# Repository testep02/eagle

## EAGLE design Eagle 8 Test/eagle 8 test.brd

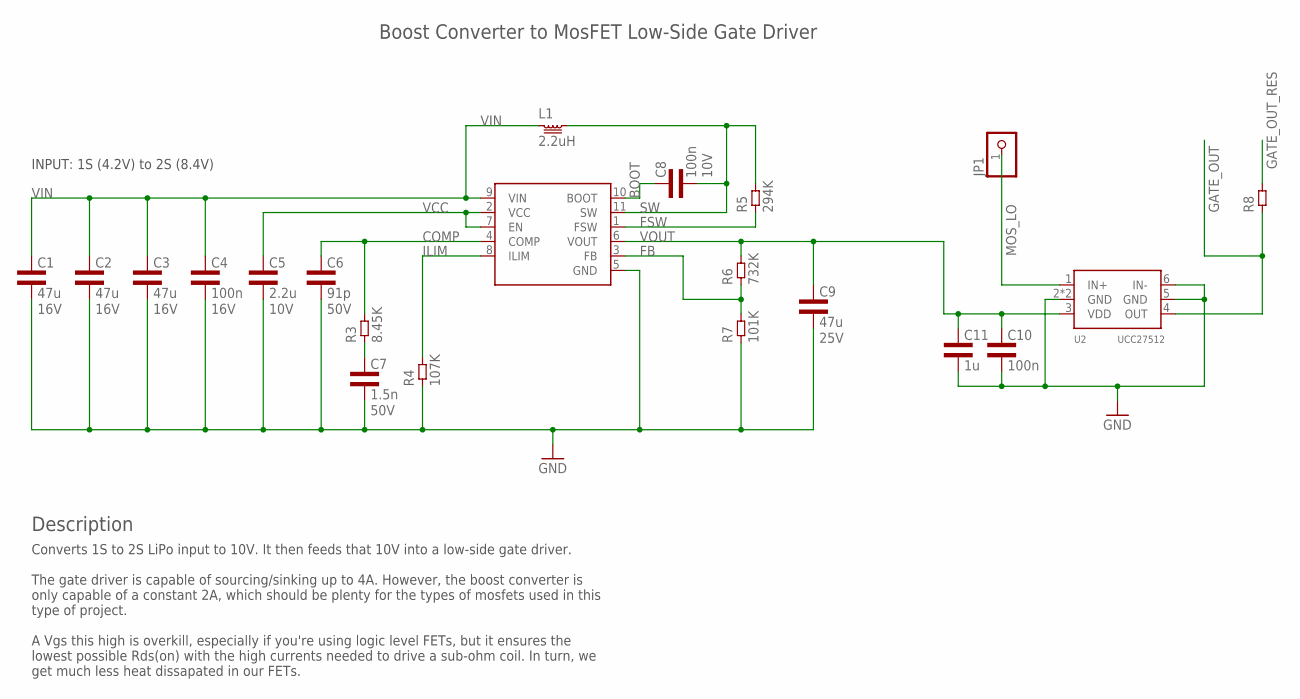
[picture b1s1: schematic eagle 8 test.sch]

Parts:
C1, C2, C3: 47u; 1210L3; VOLTAGE 16V
C4: 100n; 0402L3; VOLTAGE 16V
C5: 2.2u; 0603L3; VOLTAGE 10V
C6: 91p; 0805L3; VOLTAGE 50V
C7: 1.5n; 0805L3; VOLTAGE 50V
C8: 100n; 0402L3; VOLTAGE 10V
C9: 47u; 1206L3; VOLTAGE 25V
C10: 100n; 0603L3
C11: 1u; 0805L3
JP1: PINHD-1X1; 1X01
L1: 2.2uH; 9.2X8.5
R3: 8.45K; 0402L3
R4: 107K; 1206L3
R5: 294K; 1206L3
R6: 732K; 0402L3
R7: 101K; 0805L3
R8: RES1206L3; 1206L3
U1: TPS61089; VQFN-11
U2: UCC27512; S-PWSON-N6

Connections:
BOOT: C8.P$1 (1), U1.10 (BOOT)
COMP: C6.1, R3.P$2 (2), U1.4 (COMP)
COMP_RES: C7.1, R3.P$1 (1)
FB: R6.P$1 (1), R7.2, U1.3 (FB)
FSW: R5.1, U1.1 (FSW)
GATE_OUT: R8.1, U2.4 (OUT)
GATE_OUT_RES: R8.2
GND: C1.P$2 (2), C2.P$2 (2), C3.P$2 (2), C4.P$2 (2), C5.P$2 (2), C6.2, C7.2, C9.2, C10.P$2 (2), C11.2, R4.1, R7.1, U1.5 (GND), U2.2 (GND), U2.5 (GND), U2.6 (IN-), U2.TP (GND)
ILIM: R4.2, U1.8 (ILIM)
MOS_LO: JP1.1, U2.1 (IN+)
SW: C8.P$2 (2), L1.2, R5.2, U1.11 (SW)
VCC: C5.P$1 (1), U1.2 (VCC), U1.7 (EN)
VIN: C1.P$1 (1), C2.P$1 (1), C3.P$1 (1), C4.P$1 (1), L1.1, U1.9 (VIN)
VOUT: C9.1, C10.P$1 (1), C11.1, R6.P$2 (2), U1.6 (VOUT), U2.3 (VDD)

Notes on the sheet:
INPUT: 1S (4.2V) to 2S (8.4V)
Boost Converter to MosFET Low-Side Gate Driver
Description
Converts 1S to 2S LiPo input to 10V. It then feeds that 10V into a low-side gate driver. The gate driver is capable of sourcing/sinking up to 4A. However, the boost converter is only capable of a constant 2A, which should be plenty for the types of mosfets used in this type of project. A Vgs this h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

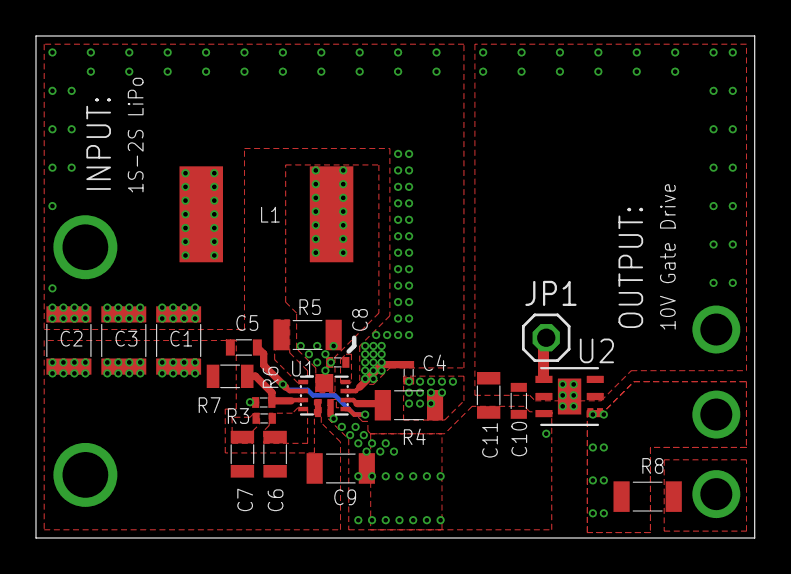
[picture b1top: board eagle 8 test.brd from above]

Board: 4 copper layers, 39.9 x 27.9 mm, 21 parts (0 on the bottom side), 13 nets.

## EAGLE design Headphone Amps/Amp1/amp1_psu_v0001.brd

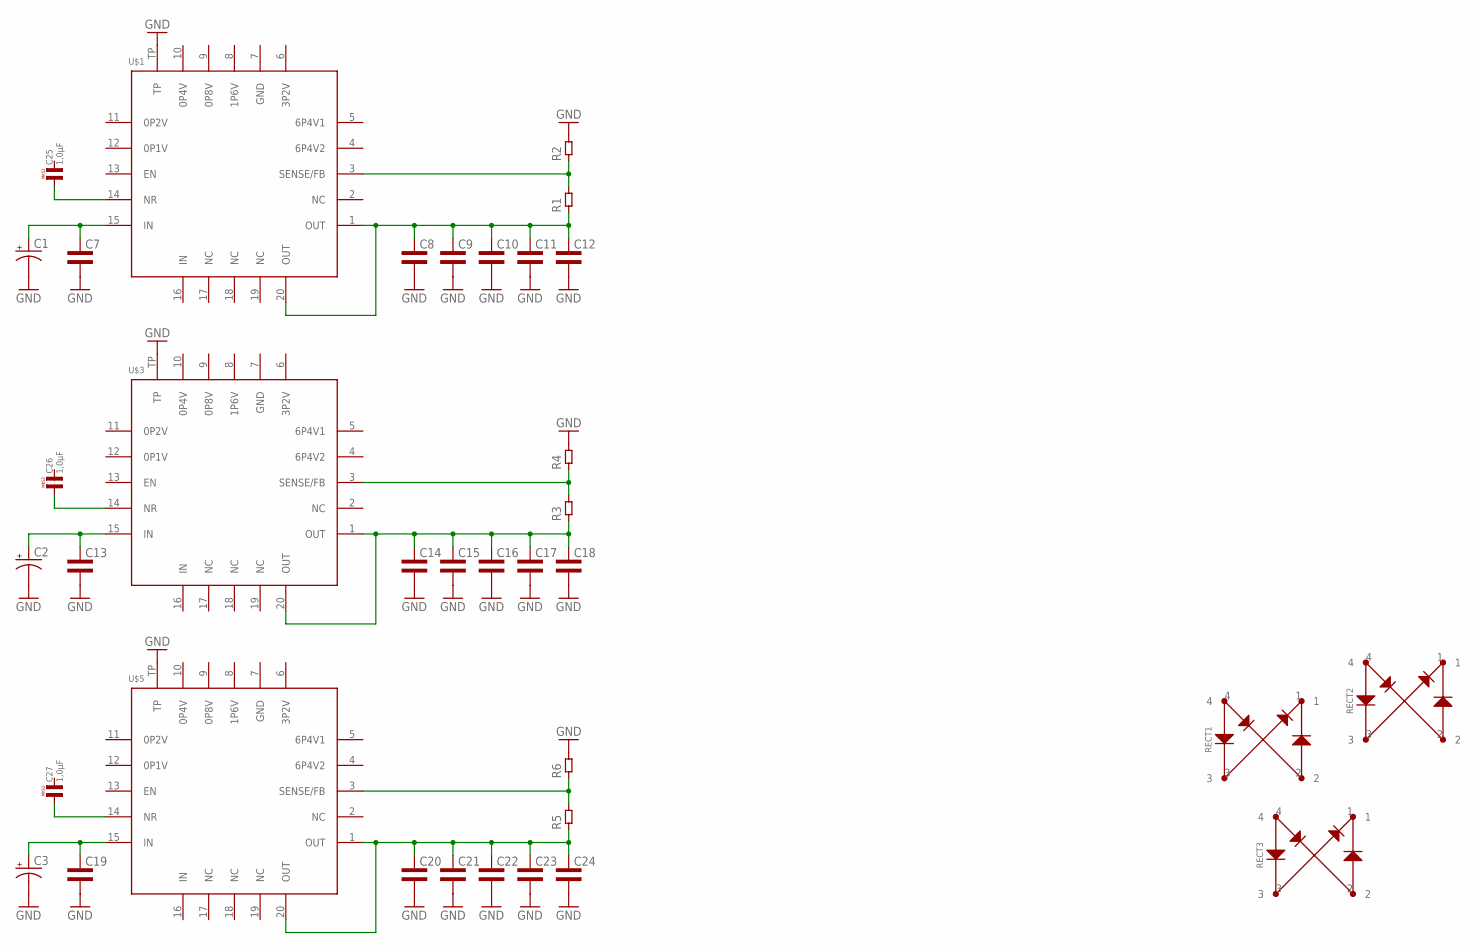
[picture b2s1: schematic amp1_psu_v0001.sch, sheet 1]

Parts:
C1, C2, C3: CPOL-USE7.5-18; E7,5-18
C7, C8, C9, C10, C11, C12, C13, C14, C15, C16, C17, C18, C19, C20, C21, C22, C23, C24: CAP0805L3; 0805L3
C25, C26, C27: 1,0µF; R5B5
R1, R2, R3, R4, R5, R6: RES0805L3; 0805L3
RECT1, RECT2, RECT3: RECTIFIER_Z4GP206; RECTIFIER_ABS-4
U$1, U$3, U$5: POWER-SUPPLY_POS_V1_TI_LDO_TPS7A4700; POWER-SUPPLY_POS_V1_TI_LDO_VQFN-20

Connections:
GND: C1.-, C2.-, C3.-, C7.2, C8.2, C9.2, C10.2, C11.2, C12.2, C13.2, C14.2, C15.2, C16.2, C17.2, C18.2, C19.2, C20.2, C21.2, C22.2, C23.2, C24.2, R2.2, R4.2, R6.2, U$1.TP, U$3.TP, U$5.TP; also elsewhere on the board
unnamed: C1.+, C7.1, U$1.15 (IN)
unnamed: C8.1, C9.1, C10.1, C11.1, C12.1, R1.1, U$1.1 (OUT), U$1.20 (OUT)
unnamed: C2.+, C13.1, U$3.15 (IN)
unnamed: C14.1, C15.1, C16.1, C17.1, C18.1, R3.1, U$3.1 (OUT), U$3.20 (OUT)
unnamed: C3.+, C19.1, U$5.15 (IN)
unnamed: C20.1, C21.1, C22.1, C23.1, C24.1, R5.1, U$5.1 (OUT), U$5.20 (OUT)
unnamed: R3.2, R4.1, U$3.3 (SENSE/FB)
unnamed: R5.2, R6.1, U$5.3 (SENSE/FB)
unnamed: R1.2, R2.1, U$1.3 (SENSE/FB)
unnamed: C25.1, U$1.14 (NR)
unnamed: C26.1, U$3.14 (NR)
unnamed: C27.1, U$5.14 (NR)

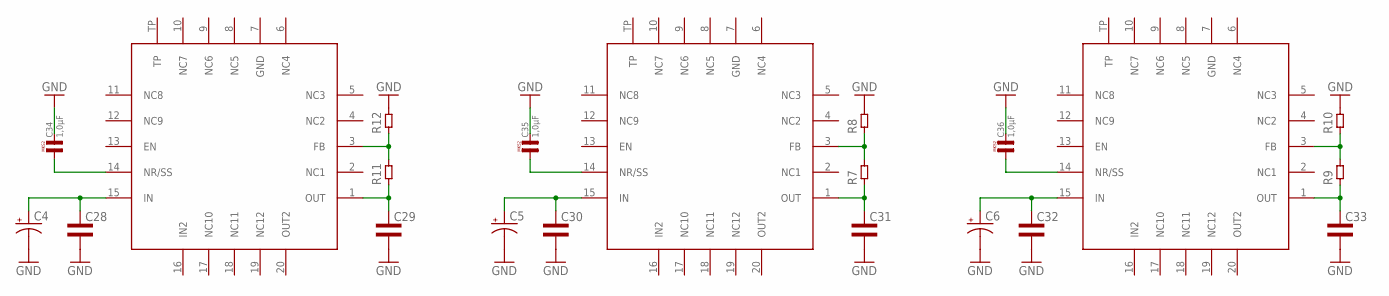
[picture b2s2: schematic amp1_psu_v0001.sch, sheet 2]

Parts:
C4, C5, C6: CPOL-USE7.5-18; E7,5-18
C28, C29, C30, C31, C32, C33: CAP0805L3; 0805L3
C34, C35, C36: 1,0µF; R5B5
R7, R8, R9, R10, R11, R12: RES0805L3; 0805L3
U$6, U$7, U$8: POWER-SUPPLY_POS_V1_TI_LDO_TPS7A3301RGWT; POWER-SUPPLY_POS_V1_TI_LDO_VQFN-20

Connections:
GND: C4.-, C5.-, C6.-, C28.2, C29.2, C30.2, C31.2, C32.2, C33.2, C34.2, C35.2, C36.2, R8.2, R10.2, R12.2; also elsewhere on the board
unnamed: C4.+, C28.1, U$6.15 (IN)
unnamed: C29.1, R11.1, U$6.1 (OUT)
unnamed: C5.+, C30.1, U$7.15 (IN)
unnamed: C31.1, R7.1, U$7.1 (OUT)
unnamed: C6.+, C32.1, U$8.15 (IN)
unnamed: C33.1, R9.1, U$8.1 (OUT)
unnamed: R11.2, R12.1, U$6.3 (FB)
unnamed: R7.2, R8.1, U$7.3 (FB)
unnamed: R9.2, R10.1, U$8.3 (FB)
unnamed: C34.1, U$6.14 (NR/SS)
unnamed: C35.1, U$7.14 (NR/SS)
unnamed: C36.1, U$8.14 (NR/SS)

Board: 2 copper layers, 57 parts (8 on the bottom side), 25 nets, no tracks yet.

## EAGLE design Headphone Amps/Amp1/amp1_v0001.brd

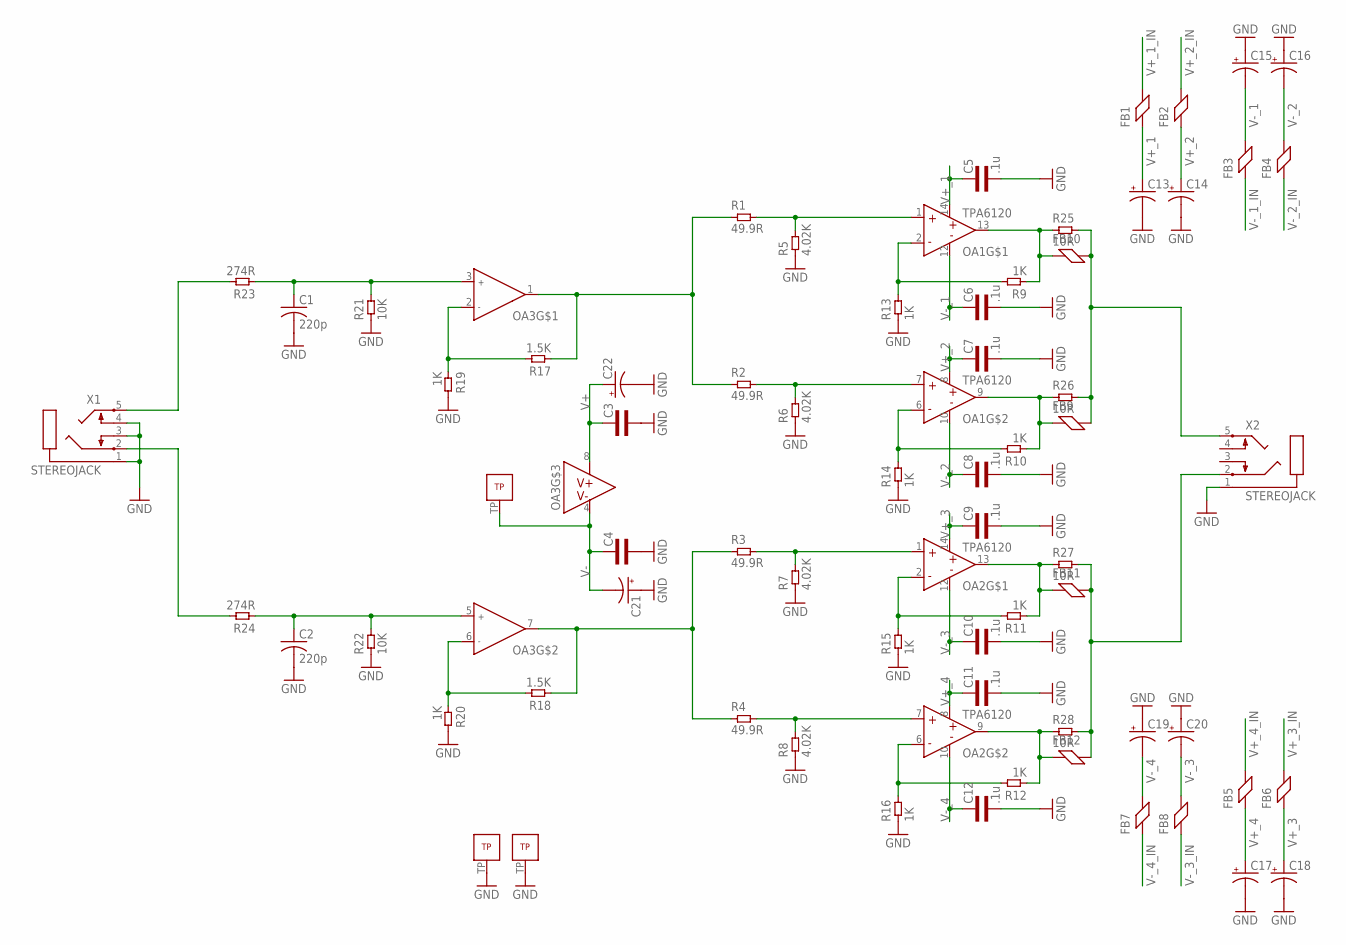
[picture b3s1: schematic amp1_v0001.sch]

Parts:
C1, C2: 220p; C025-025X050
C3, C4: CAP0603L3; 0603L3
C5, C6, C7, C8, C9, C10, C11, C12: .1u; 0603L3
C13, C14, C15, C16, C17, C18, C19, C20, C21, C22: CPOL-USE2-5; E2-5
FB1, FB2, FB3, FB4, FB5, FB6, FB7, FB8, FB9, FB10, FB11, FB12: FERRITE0805L3; 0805L3
OA1, OA2: TPA6120QFN; S-PVQFN-N14
OA3: OPA1612; S-PWSON-N8
R1, R2, R3, R4: 49.9R; 0805L3
R5, R6, R7, R8: 4.02K; 0805L3
R9, R10, R11, R12, R13, R14, R15, R16, R19, R20: 1K; 0805L3
R17, R18: 1.5K; 0805L3
R21, R22: 10K; 0805L3
R23, R24: 274R; 0805L3
R25, R26, R27, R28: 10R; 1206L3
X1, X2: STEREOJACK; STX3100

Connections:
GND: C1.2, C2.2, C3.P$2 (2), C4.P$2 (2), C5.P$2 (2), C6.P$2 (2), C7.P$2 (2), C8.P$2 (2), C9.P$2 (2), C10.P$2 (2), C11.P$2 (2), C12.P$2 (2), C13.-, C14.-, C15.+, C16.+, C17.-, C18.-, C19.+, C20.+, C21.+, C22.-, OA1.TP, OA2.TP, R5.1, R6.1, R7.1, R8.1, R13.1, R14.1, R15.1, R16.1, R19.2, R20.2, R21.1, R22.1, X1.1, X1.3, X1.4, X2.1
unnamed: OA1.1 (IN+), R1.2, R5.2
unnamed: OA1.7 (IN+), R2.2, R6.2
unnamed: OA2.1 (IN+), R3.2, R7.2
unnamed: OA2.7 (IN+), R4.2, R8.2
unnamed: FB11.1, OA2.13 (OUT), R11.1, R27.1
unnamed: FB12.1, OA2.9 (OUT), R12.1, R28.1
unnamed: FB9.1, OA1.9 (OUT), R10.1, R26.1
unnamed: FB10.1, OA1.13 (OUT), R9.1, R25.1
unnamed: OA1.2 (IN-), R9.2, R13.2
unnamed: OA1.6 (IN-), R10.2, R14.2
unnamed: OA2.2 (IN-), R11.2, R15.2
unnamed: OA2.6 (IN-), R12.2, R16.2
unnamed: FB9.2, FB10.2, R25.2, R26.2, X2.5
unnamed: OA3.1 (OUTA), R1.1, R2.1, R17.1
unnamed: FB11.2, FB12.2, R27.2, R28.2, X2.2
unnamed: OA3.7 (OUTB), R3.1, R4.1, R18.1
unnamed: OA3.6 (INB-), R18.2, R20.1
unnamed: OA3.2 (INA-), R17.2, R19.1
unnamed: C1.1, OA3.3 (INA+), R21.2, R23.1
unnamed: C2.1, OA3.5 (INB+), R22.2, R24.1
unnamed: R24.2, X1.2
unnamed: R23.2, X1.5
V+: C3.P$1 (1), C22.+, OA3.8 (V+)
V+_1: C5.P$1 (1), C13.+, FB1.1, OA1.14 (V+)
V+_1_IN: FB1.2
V+_2: C7.P$1 (1), C14.+, FB2.1, OA1.8 (V+)
V+_2_IN: FB2.2
V+_3: C9.P$1 (1), C18.+, FB6.1, OA2.14 (V+)
V+_3_IN: FB6.2
V+_4: C11.P$1 (1), C17.+, FB5.1, OA2.8 (V+)
V+_4_IN: FB5.2
V-: C4.P$1 (1), C21.-, OA3.4 (V-), OA3.TP
V-_1: C6.P$1 (1), C15.-, FB3.2, OA1.12 (V-)
V-_1_IN: FB3.1
V-_2: C8.P$1 (1), C16.-, FB4.2, OA1.10 (V-)
V-_2_IN: FB4.1
V-_3: C10.P$1 (1), C20.-, FB8.2, OA2.12 (V-)
V-_3_IN: FB8.1
V-_4: C12.P$1 (1), C19.-, FB7.2, OA2.10 (V-)
V-_4_IN: FB7.1

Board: 2 copper layers, 67 parts (9 on the bottom side), 33 nets, no tracks yet.

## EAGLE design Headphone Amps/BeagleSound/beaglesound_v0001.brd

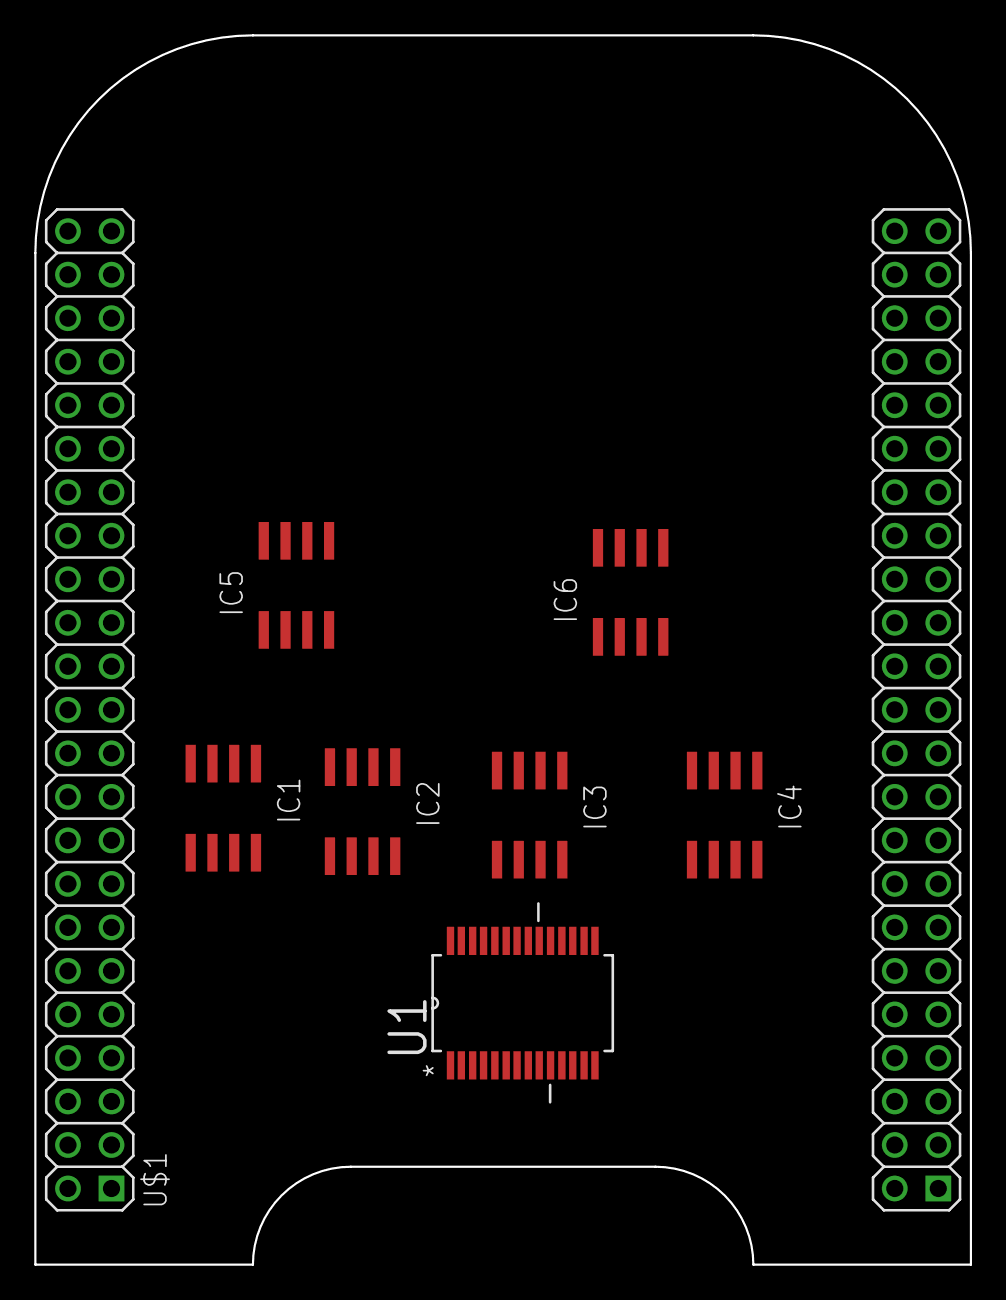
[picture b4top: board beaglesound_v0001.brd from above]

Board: 2 copper layers, 54.6 x 71.8 mm, 8 parts (0 on the bottom side), 3 nets, no tracks yet.

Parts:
IC1, IC2, IC3, IC4, IC5, IC6: AD8610R; SO8
U1: PCM1794ADB; SOP65P780X200-28N
U$1: BEAGLEBONE_OUTLINE; BEAGLEBONE_SHIELD

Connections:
GND: U$1.1, U$1.2, U$1.47, U$1.48, U$1.89, U$1.90, U$1.91, U$1.92
VDD_3V3EXP: U$1.49, U$1.50
VDD_5V: U$1.51, U$1.52

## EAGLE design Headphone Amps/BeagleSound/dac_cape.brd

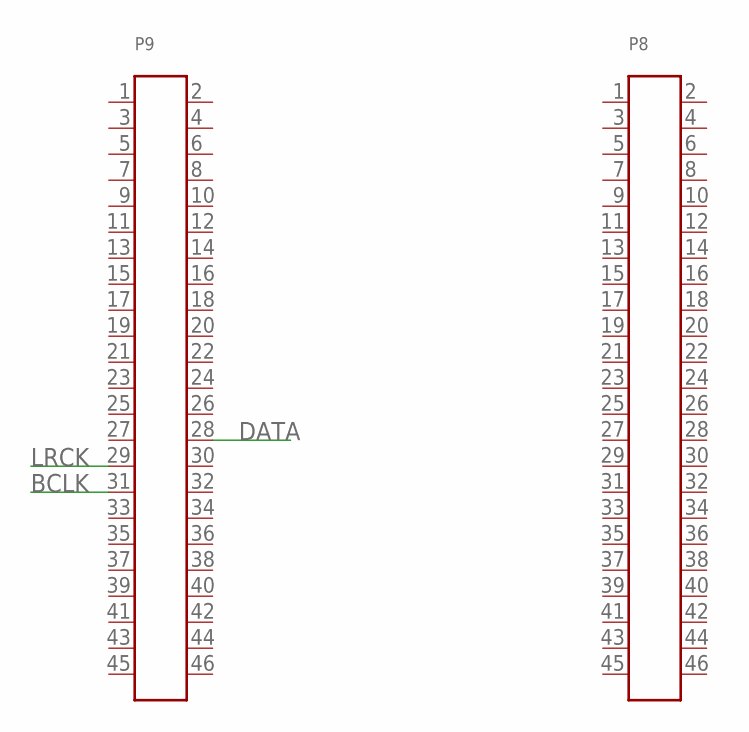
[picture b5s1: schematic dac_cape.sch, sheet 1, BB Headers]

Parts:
P8, P9: PINHD-2X23; 2X23

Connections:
BCLK: P9.31; also elsewhere on the board
DATA: P9.28; also elsewhere on the board
LRCK: P9.29; also elsewhere on the board

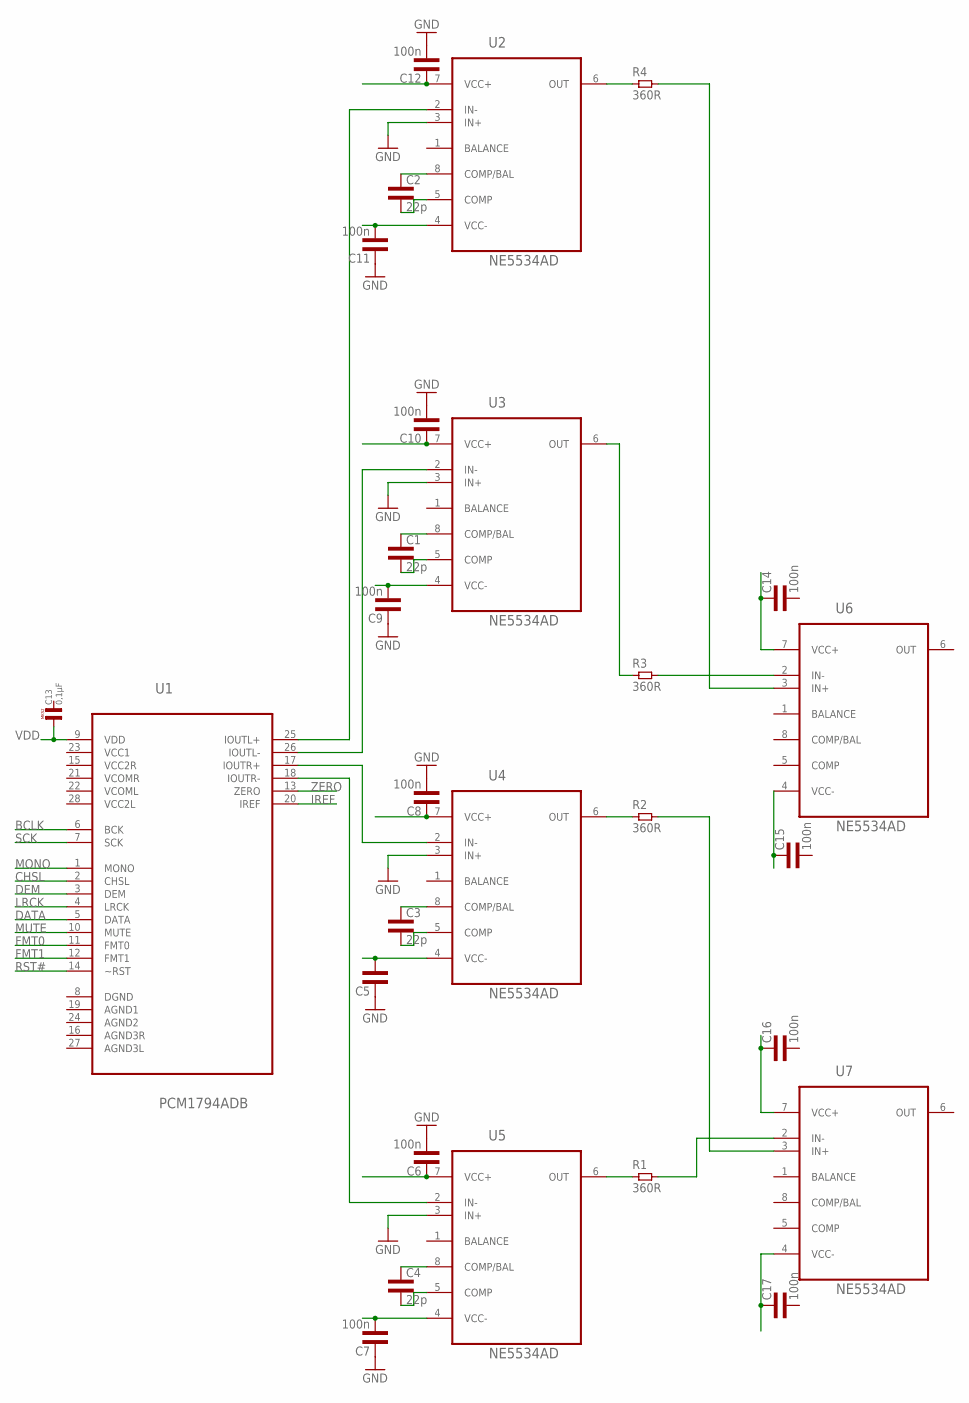
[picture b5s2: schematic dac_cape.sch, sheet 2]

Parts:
C1, C2, C3, C4: 22p; 0603L3
C5: CAP0603L3; 0603L3
C6, C7, C8, C9, C10, C11, C12, C14, C15, C16, C17: 100n; 0603L3
C13: 0,1µF; R5B3
R1, R2, R3, R4: 360R; 0603L3
U1: PCM1794ADB; SOP65P780X200-28N
U2, U3, U4, U5, U6, U7: NE5534AD; SOIC127P600X175-8N

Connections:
BCLK: U1.6 (BCK); also elsewhere on the board
CHSL: U1.2 (CHSL)
DATA: U1.5 (DATA); also elsewhere on the board
DEM: U1.3 (DEM)
FMT0: U1.11 (FMT0)
FMT1: U1.12 (FMT1)
GND: C5.P$1 (1), C6.P$2 (2), C7.P$1 (1), C8.P$2 (2), C9.P$1 (1), C10.P$2 (2), C11.P$1 (1), C12.P$2 (2), U2.3 (IN+), U3.3 (IN+), U4.3 (IN+), U5.3 (IN+)
IREF: U1.20 (IREF)
LRCK: U1.4 (LRCK); also elsewhere on the board
MONO: U1.1 (MONO)
MUTE: U1.10 (MUTE)
unnamed: U1.26 (IOUTL-), U3.2 (IN-)
unnamed: U1.17 (IOUTR+), U4.2 (IN-)
unnamed: U1.18 (IOUTR-), U5.2 (IN-)
unnamed: U1.25 (IOUTL+), U2.2 (IN-)
unnamed: R3.P$2 (2), U6.2 (IN-)
unnamed: R1.P$2 (2), U7.2 (IN-)
unnamed: R4.P$1 (1), U2.6 (OUT)
unnamed: R3.P$1 (1), U3.6 (OUT)
unnamed: R4.P$2 (2), U6.3 (IN+)
unnamed: R2.P$2 (2), U7.3 (IN+)
unnamed: R2.P$1 (1), U4.6 (OUT)
unnamed: R1.P$1 (1), U5.6 (OUT)
unnamed: C3.P$1 (1), U4.8 (COMP/BAL)
unnamed: C3.P$2 (2), U4.5 (COMP)
unnamed: C4.P$1 (1), U5.8 (COMP/BAL)
unnamed: C4.P$2 (2), U5.5 (COMP)
unnamed: C2.P$1 (1), U2.8 (COMP/BAL)
unnamed: C2.P$2 (2), U2.5 (COMP)
unnamed: C1.P$1 (1), U3.8 (COMP/BAL)
unnamed: C1.P$2 (2), U3.5 (COMP)
unnamed: C12.P$1 (1), U2.7 (VCC+)
unnamed: C11.P$2 (2), U2.4 (VCC-)
unnamed: C10.P$1 (1), U3.7 (VCC+)
unnamed: C9.P$2 (2), U3.4 (VCC-)
unnamed: C8.P$1 (1), U4.7 (VCC+)
unnamed: C5.P$2 (2), U4.4 (VCC-)
unnamed: C6.P$1 (1), U5.7 (VCC+)
unnamed: C7.P$2 (2), U5.4 (VCC-)
unnamed: C14.P$1 (1), U6.7 (VCC+)
unnamed: C15.P$1 (1), U6.4 (VCC-)
unnamed: C16.P$1 (1), U7.7 (VCC+)
unnamed: C17.P$1 (1), U7.4 (VCC-)
RST#: U1.14 (~RST)
SCK: U1.7 (SCK)
VCC1: U1.23 (VCC1)
VCC2L: U1.28 (VCC2L)
VCC2R: U1.15 (VCC2R)
VDD: C13.1, U1.9 (VDD)
ZERO: U1.13 (ZERO)

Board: 4 copper layers, 30 parts (0 on the bottom side), 37 nets, no tracks yet.

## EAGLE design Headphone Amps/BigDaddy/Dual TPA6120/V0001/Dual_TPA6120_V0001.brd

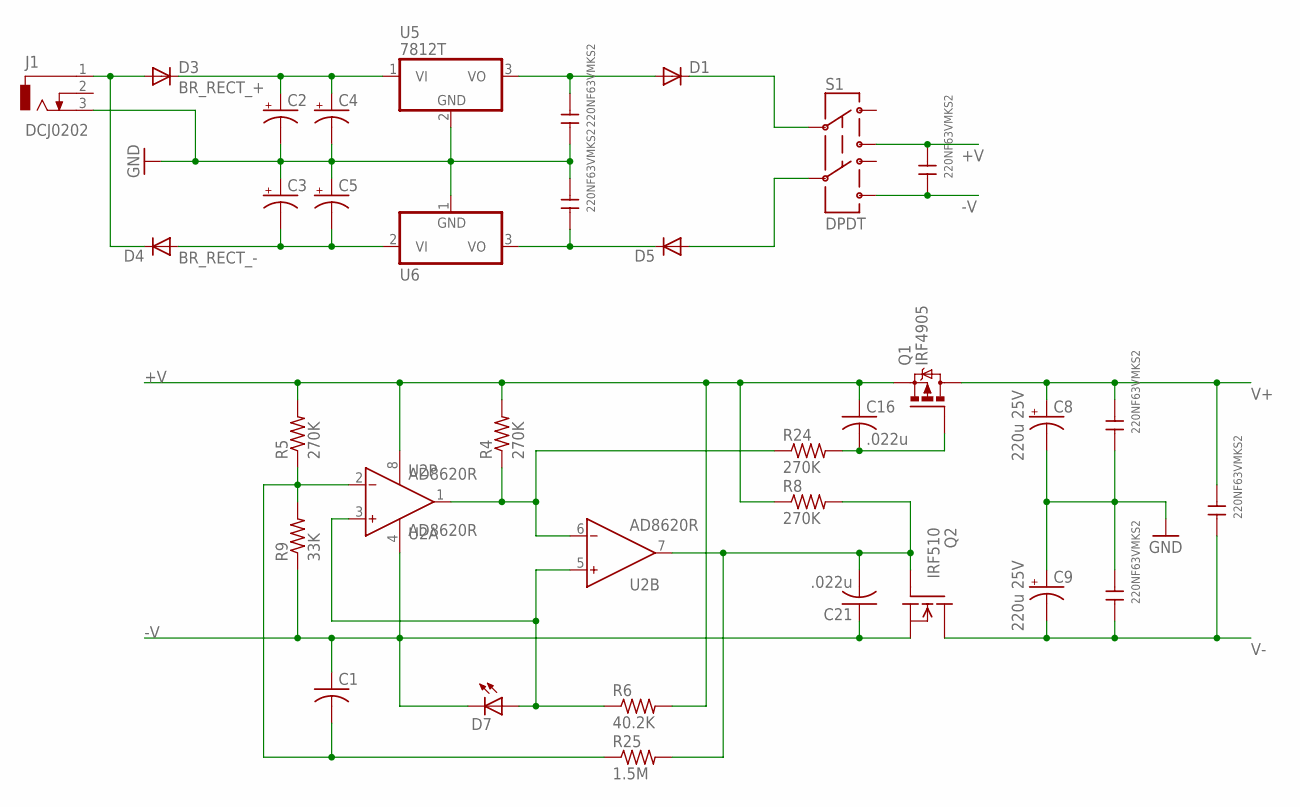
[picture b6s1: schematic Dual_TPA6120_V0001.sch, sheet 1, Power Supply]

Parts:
C1: C-USC0603; C0603
C2, C3, C4, C5: CPOL-USE7.5-16; E7,5-16
C6, C7, C10, C15, C17, C18: 220NF63VMKS2; 3,0X7,5RM5,0
C8, C9: 220u 25V; E3,5-10
C16, C21: .022u; C0603
D1, D3, D4, D5: 1N5060GP; DO15-12
D7: LED3MM
J1: DCJ0202
Q1: IRF4905; TO220BH
Q2: IRF510; TO220
R4, R5, R8, R24: 270K; R0805
R6: 40.2K; R0805
R9: 33K; R0805
R25: 1.5M; R0805
S1: DPDT; AYZ0202
U2: AD8620R; SO8
U5: 7812T; TO220H
U6: 7912T; TO220H

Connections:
+V: C15.2, C16.1, Q1.S, R4.2, R5.2, R6.2, R8.1, S1.3, U2.8 (V+)
-V: C1.1, C15.1, C21.1, D7.K (C), Q2.3 (S), R9.1, S1.6, U2.4 (V-)
BR_RECT_+: C2.+, C4.+, D3.C, U5.1 (VI)
BR_RECT_-: C3.-, C5.-, D4.A, U6.2 (VI)
GND: C2.-, C3.+, C4.-, C5.+, C6.1, C7.2, C8.-, C9.+, C17.1, C18.2, J1.3, U5.2 (GND), U6.1 (GND); also elsewhere on the board
unnamed: C6.2, D1.A, U5.3 (VO)
unnamed: C1.2, R5.1, R9.2, R25.1, U2.2 (IN-)
unnamed: C7.1, D5.C, U6.3 (VO)
unnamed: D7.A, R6.1, U2.3 (IN+), U2.5 (IN+)
unnamed: C21.2, Q2.1 (G), R8.2, R25.2, U2.7 (OUT)
unnamed: R4.1, R24.1, U2.1 (OUT), U2.6 (IN-)
unnamed: C16.2, Q1.G, R24.2
unnamed: D3.A, D4.C, J1.1
REG+: D1.C, S1.2
REG-: D5.A, S1.5
V+: C8.+, C10.2, C17.2, Q1.D; also elsewhere on the board
V-: C9.-, C10.1, C18.1, Q2.2 (D); also elsewhere on the board

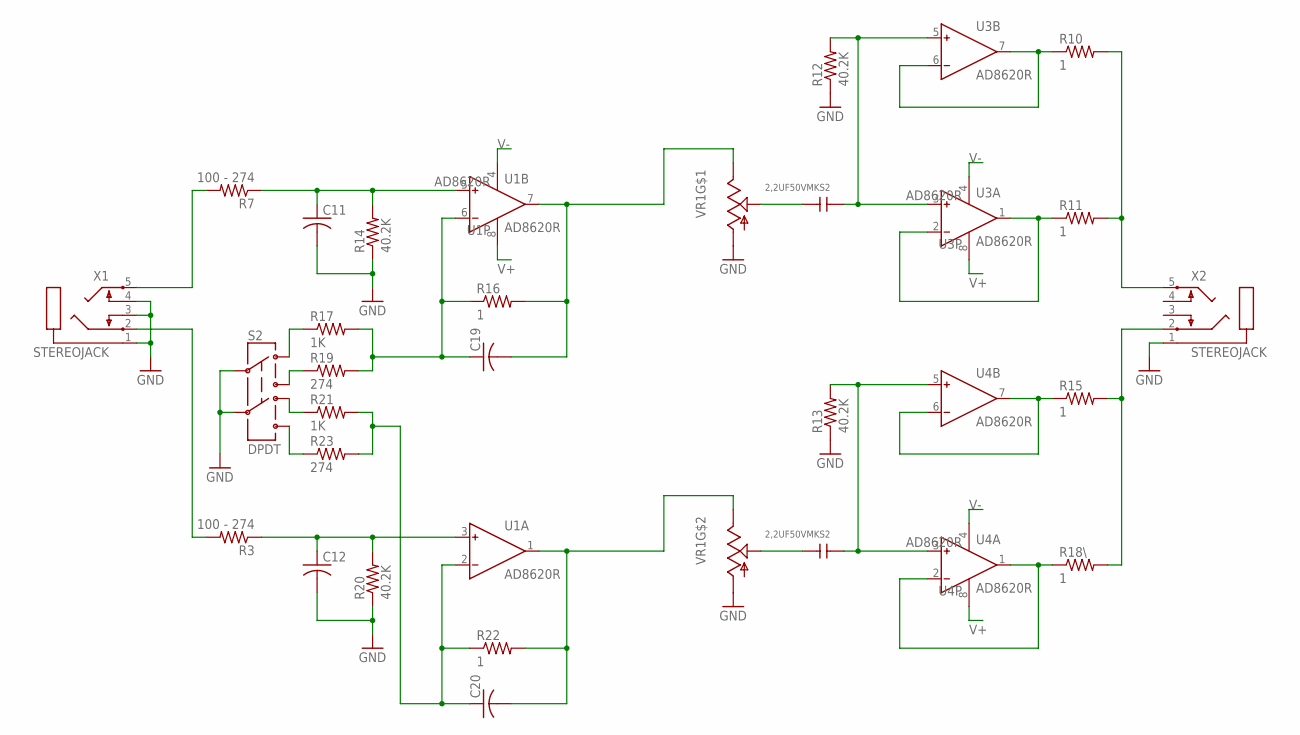
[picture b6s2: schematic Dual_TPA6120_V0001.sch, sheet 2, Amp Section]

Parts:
C11, C12, C19, C20: C-USC0603; C0603
C13, C14: 2,2UF50VMKS2; 7,2X13,0RM5,0
R3, R7: 100 - 274; R1206
R10, R11, R15, R16, R18\, R22: 1; R1206
R12, R13, R14, R20: 40.2K; R1206
R17, R21: 1K; R1206
R19, R23: 274; R1206
S2: DPDT; AYZ0202
U1, U3, U4: AD8620R; SO8
VR1: ALPS_BLUE; ALPS_RK27
X1, X2: STEREOJACK; STX3100

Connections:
GND: C11.2, C12.2, R12.1, R13.1, R14.1, R20.1, S2.2, S2.5, VR1.G1 (1), VR1.G2 (1), X1.1, X1.3, X1.4, X2.1; also elsewhere on the board
unnamed: R10.1, U3.6 (IN-), U3.7 (OUT)
unnamed: R11.1, U3.1 (OUT), U3.2 (IN-)
unnamed: R15.1, U4.6 (IN-), U4.7 (OUT)
unnamed: R18\.1, U4.1 (OUT), U4.2 (IN-)
unnamed: C19.2, R16.2, U1.7 (OUT), VR1.I1 (3)
unnamed: C20.2, R22.2, U1.1 (OUT), VR1.I2 (3)
unnamed: C14.2, VR1.O2 (2)
unnamed: R10.2, R11.2, X2.5
unnamed: R15.2, R18\.2, X2.2
unnamed: C13.1, R12.2, U3.3 (IN+), U3.5 (IN+)
unnamed: C14.1, R13.2, U4.3 (IN+), U4.5 (IN+)
unnamed: C13.2, VR1.O1 (2)
unnamed: R7.2, X1.5
unnamed: R3.2, X1.2
unnamed: C11.1, R7.1, R14.2, U1.5 (IN+)
unnamed: C12.1, R3.1, R20.2, U1.3 (IN+)
unnamed: C19.1, R16.1, R17.2, R19.2, U1.6 (IN-)
unnamed: C20.1, R21.2, R22.1, R23.2, U1.2 (IN-)
unnamed: R17.1, S2.1
unnamed: R19.1, S2.3
unnamed: R21.1, S2.4
unnamed: R23.1, S2.6
V+: U1.8 (V+), U3.8 (V+), U4.8 (V+); also elsewhere on the board
V-: U1.4 (V-), U3.4 (V-), U4.4 (V-); also elsewhere on the board

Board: 2 copper layers, 63 parts (0 on the bottom side), 39 nets, no tracks yet.

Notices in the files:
parts and their libraries:
SparkFun-Aesthetics: Licensing: CC v3.0 Share-Alike You are welcome to use this library for commercial purposes.
